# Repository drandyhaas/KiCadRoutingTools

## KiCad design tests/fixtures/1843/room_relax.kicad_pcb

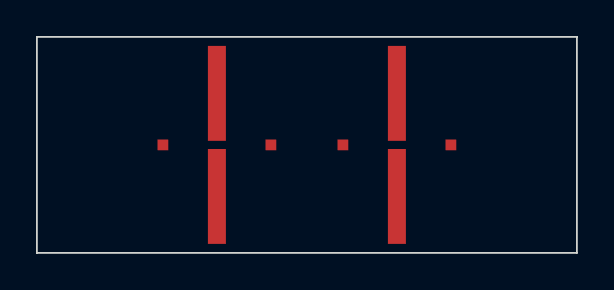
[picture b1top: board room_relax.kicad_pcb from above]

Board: 4 copper layers, 30.0 x 12.0 mm, 4 parts (0 on the bottom side), 4 nets, no tracks yet.

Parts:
P1: P1
P2: P2
W1: W1
W2: W2

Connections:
OPEN_NET: P2.1, P2.2
ROOM_NET: P1.1, P1.2
WALL_IN: W1.1, W1.2
WALL_OUT: W2.1, W2.2

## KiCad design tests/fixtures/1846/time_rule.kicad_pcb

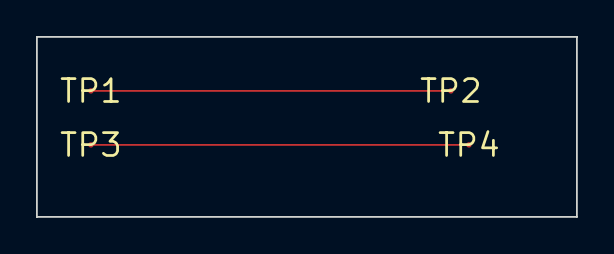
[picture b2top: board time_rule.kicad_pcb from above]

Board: 4 copper layers, 30.0 x 10.0 mm, 4 parts (0 on the bottom side), 2 nets.

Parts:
TP1: TP1
TP2: TP2
TP3: TP3
TP4: TP4

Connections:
P: TP1.1, TP2.1
Q: TP3.1, TP4.1
